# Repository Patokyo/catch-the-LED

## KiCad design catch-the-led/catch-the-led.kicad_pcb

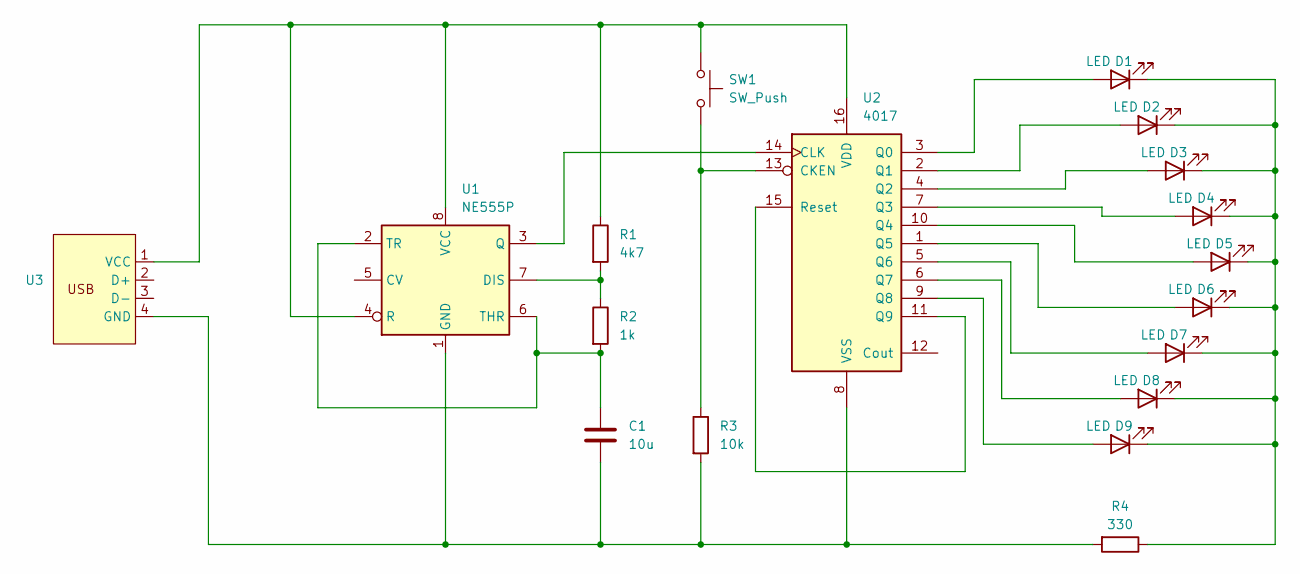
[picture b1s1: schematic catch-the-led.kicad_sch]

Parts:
C1: 10u; C_0805_2012Metric_Pad1.18x1.45mm_HandSolder
D1, D2, D3, D4, D5, D6, D7, D8, D9: LED; LED_1210_3225Metric_Pad1.42x2.65mm_HandSolder
R1: 4k7; R_0805_2012Metric_Pad1.20x1.40mm_HandSolder
R2: 1k; R_0805_2012Metric_Pad1.20x1.40mm_HandSolder
R3: 10k; R_0805_2012Metric_Pad1.20x1.40mm_HandSolder
R4: 330; R_0805_2012Metric_Pad1.20x1.40mm_HandSolder
SW1: SW_Push; SW_SPST_TS-1088-xR020
U1: NE555P; DIP-8_W7.62mm
U2: 4017; DIP-16_W7.62mm
U3: PCB_USB_connector

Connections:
unnamed: D1.2 (A), U2.3 (Q0)
unnamed: D1.1 (K), D2.1 (K), D3.1 (K), D4.1 (K), D5.1 (K), D6.1 (K), D7.1 (K), D8.1 (K), D9.1 (K), R4.1
unnamed: D2.2 (A), U2.2 (Q1)
unnamed: D3.2 (A), U2.4 (Q2)
unnamed: D4.2 (A), U2.7 (Q3)
unnamed: D5.2 (A), U2.10 (Q4)
unnamed: D6.2 (A), U2.1 (Q5)
unnamed: D7.2 (A), U2.5 (Q6)
unnamed: D8.2 (A), U2.6 (Q7)
unnamed: D9.2 (A), U2.9 (Q8)
unnamed: R1.2, R2.1, U1.7 (DIS)
unnamed: C1.2, R3.2, R4.2, U1.1 (GND), U2.8 (VSS), U3.4 (GND)
unnamed: U1.3 (Q), U2.14 (CLK)
unnamed: R1.1, SW1.1, U1.4 (R), U1.8 (VCC), U2.16 (VDD), U3.1 (VCC)
unnamed: C1.1, R2.2, U1.2 (TR), U1.6 (THR)
unnamed: R3.1, SW1.2, U2.13 (CKEN)
unnamed: U2.11 (Q9), U2.15 (Reset)

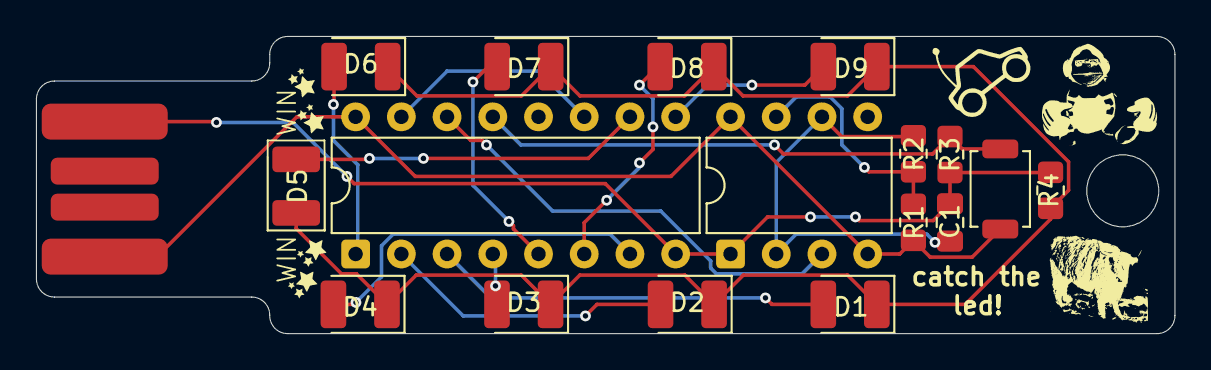
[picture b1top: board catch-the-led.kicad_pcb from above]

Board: 2 copper layers, 63.3 x 16.5 mm, 22 parts (0 on the bottom side), 17 nets.

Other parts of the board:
G: LOGO; stars
G#2, G#3, G#4: LOGO; stars

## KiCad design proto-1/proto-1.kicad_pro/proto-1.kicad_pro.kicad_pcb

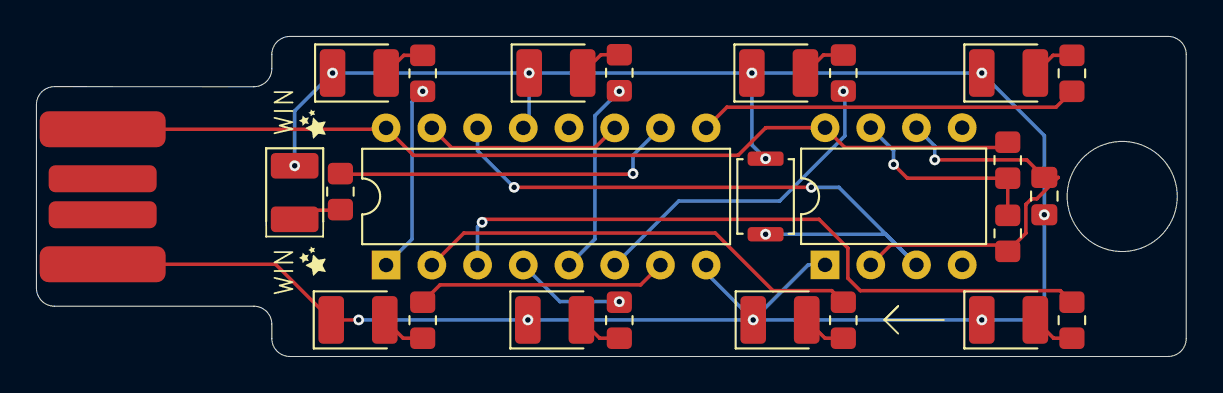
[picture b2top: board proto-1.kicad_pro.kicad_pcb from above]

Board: 2 copper layers, 63.9 x 17.8 mm, 25 parts (0 on the bottom side), 24 nets.

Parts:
C1: C; C_0805_2012Metric_Pad1.18x1.45mm_HandSolder
D1, D2, D3, D4, D5, D6, D7, D8, D9: LED; LED_1210_3225Metric_Pad1.42x2.65mm_HandSolder
R1, R2: R; R_0805_2012Metric_Pad1.20x1.40mm_HandSolder
R3, R4, R5, R6, R7, R8, R9, R10, R11: 330; R_0805_2012Metric_Pad1.20x1.40mm_HandSolder
SW1: SW_Push; SW_Push_SPST_NO_Alps_SKRK
U1: NE555P; DIP-8_W7.62mm
U2: 4017; DIP-16_W7.62mm
U3: PCB_USB_connector

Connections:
unnamed: D1.2 (A), R3.1
unnamed: C1.2, D1.1 (K), D2.1 (K), D3.1 (K), D4.1 (K), D5.1 (K), D6.1 (K), D7.1 (K), D8.1 (K), D9.1 (K), SW1.1, U1.1 (GND), U2.8 (VSS), U2.13 (CKEN), U3.4 (GND)
unnamed: D2.2 (A), R4.1
unnamed: D3.2 (A), R5.1
unnamed: D4.2 (A), R6.1
unnamed: D5.2 (A), R7.1
unnamed: D6.2 (A), R8.1
unnamed: D7.2 (A), R9.1
unnamed: D8.2 (A), R10.1
unnamed: D9.2 (A), R11.1
unnamed: R1.2, R2.1, U1.7 (DIS)
unnamed: SW1.2, U1.3 (Q), U2.14 (CLK)
unnamed: R1.1, U1.4 (R), U1.8 (VCC), U2.16 (VDD), U3.1 (VCC)
unnamed: C1.1, R2.2, U1.2 (TR), U1.6 (THR)
unnamed: R3.2, U2.3 (Q0)
unnamed: R4.2, U2.2 (Q1)
unnamed: R5.2, U2.4 (Q2)
unnamed: R6.2, U2.7 (Q3)
unnamed: R7.2, U2.10 (Q4)
unnamed: R8.2, U2.1 (Q5)
unnamed: R9.2, U2.5 (Q6)
unnamed: R10.2, U2.6 (Q7)
unnamed: R11.2, U2.9 (Q8)
unnamed: U2.11 (Q9), U2.15 (Reset)

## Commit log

2025-11-06 fixed schematic
2025-11-06 finished v2
